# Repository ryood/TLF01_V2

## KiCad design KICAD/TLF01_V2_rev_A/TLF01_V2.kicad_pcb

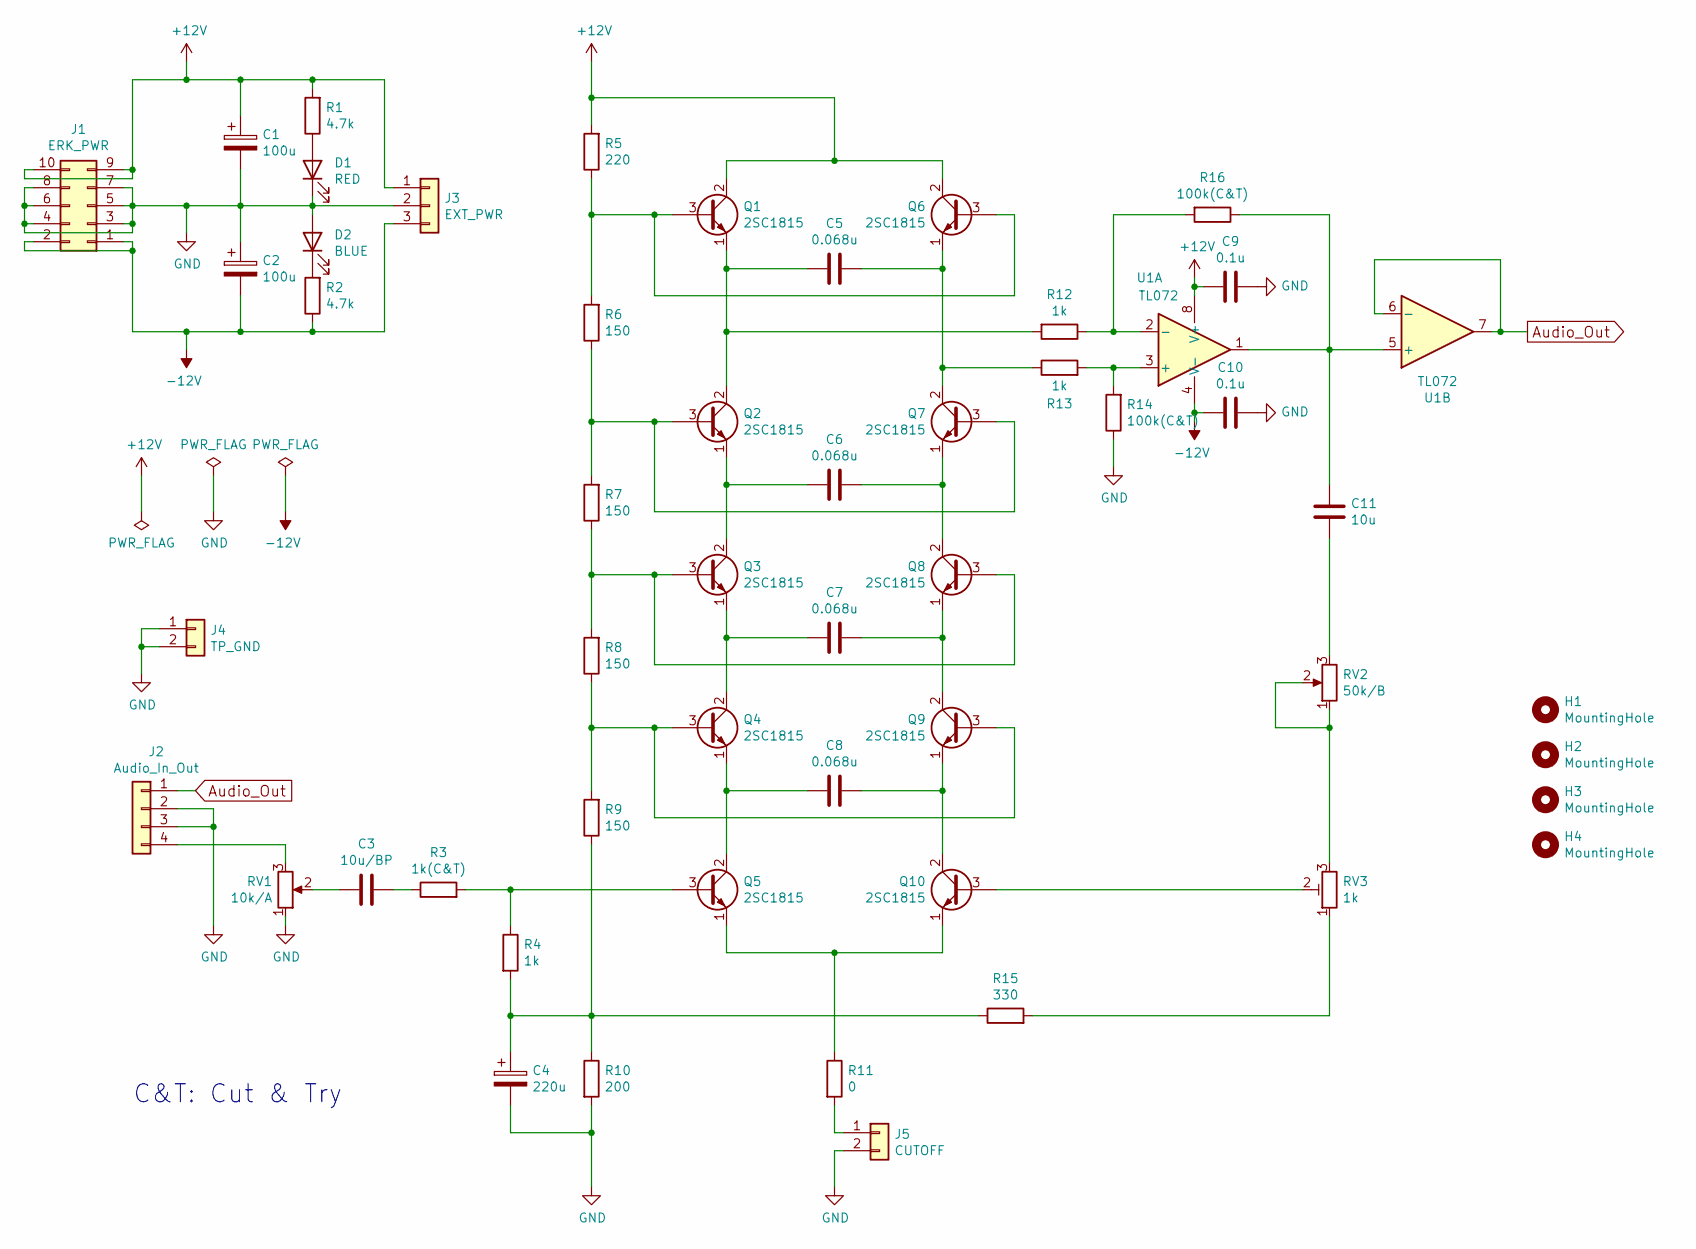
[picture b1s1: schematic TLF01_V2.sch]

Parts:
C1, C2: 100u; CP_Radial_D8.0mm_P2.50mm
C3: 10u/BP; CP_Radial_D6.3mm_P2.50mm
C4: 220u; CP_Radial_D8.0mm_P2.50mm
C5, C6, C7, C8: 0.068u; C_Rect_L10.0mm_W4.0mm_P7.50mm_MKS4
C9, C10: 0.1u; C_Disc_D3.0mm_W1.6mm_P2.50mm
C11: 10u; C_Radial_D10.0mm_H12.5mm_P5.00mm
D1: RED; LED_D3.0mm
D2: BLUE; LED_D3.0mm
H1, H2, H3, H4: MountingHole; MountingHole_3.2mm_M3
J1: ERK_PWR; IDC-Header_2x05_P2.54mm_Vertical
J2: Audio_In_Out; JST_XH_B4B-XH-A_1x04_P2.50mm_Vertical
J3: EXT_PWR; JST_XH_B3B-XH-A_1x03_P2.50mm_Vertical
J4: TP_GND; PinHeader_1x02_P2.54mm_Vertical
J5: CUTOFF; JST_XH_B2B-XH-A_1x02_P2.50mm_Vertical
Q1, Q2, Q3, Q4, Q5, Q6, Q7, Q8, Q9, Q10: 2SC1815; TO-92_Wide
R1, R2: 4.7k; R_Axial_DIN0207_L6.3mm_D2.5mm_P7.62mm_Horizontal
R3: 1k(C&T); R_Axial_DIN0207_L6.3mm_D2.5mm_P7.62mm_Horizontal
R4, R12, R13: 1k; R_Axial_DIN0207_L6.3mm_D2.5mm_P7.62mm_Horizontal
R5: 220; R_Axial_DIN0207_L6.3mm_D2.5mm_P7.62mm_Horizontal
R6, R7, R8, R9: 150; R_Axial_DIN0207_L6.3mm_D2.5mm_P7.62mm_Horizontal
R10: 200; R_Axial_DIN0207_L6.3mm_D2.5mm_P7.62mm_Horizontal
R11: 0; R_Axial_DIN0207_L6.3mm_D2.5mm_P7.62mm_Horizontal
R14, R16: 100k(C&T); R_Axial_DIN0207_L6.3mm_D2.5mm_P7.62mm_Horizontal
R15: 330; R_Axial_DIN0207_L6.3mm_D2.5mm_P7.62mm_Horizontal
RV1: 10k/A; Potentiometer_Alps_RK097_Single_Horizontal
RV2: 50k/B; Potentiometer_Alps_RK097_Single_Horizontal
RV3: 1k; Potentiometer_Bourns_3362P_Vertical
U1: TL072; DIP-8_W7.62mm_LongPads

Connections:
+12V: C1.1, C9.2, J1.9, J1.10, J3.1, Q1.2 (C), Q6.2 (C), R1.2, R5.2, U1.8 (V+)
-12V: C2.2, C10.2, J1.1, J1.2, J3.3, R2.1, U1.4 (V-)
Audio_Out: J2.1, U1.6 (-), U1.7
GND: C1.2, C2.1, C4.2, C9.1, C10.1, D1.1 (K), D2.2 (A), J1.3, J1.4, J1.5, J1.6, J1.7, J1.8, J2.2, J2.3, J3.2, J4.1, J4.2, J5.2, R10.2, R14.1, RV1.1
unnamed: C3.1, R3.1
unnamed: C3.2, RV1.2
unnamed: C4.1, R4.2, R9.1, R10.1, R15.1
unnamed: C5.1, Q6.1 (E), Q7.2 (C), R13.1
unnamed: C5.2, Q1.1 (E), Q2.2 (C), R12.2
unnamed: C6.1, Q7.1 (E), Q8.2 (C)
unnamed: C6.2, Q2.1 (E), Q3.2 (C)
unnamed: C7.1, Q8.1 (E), Q9.2 (C)
unnamed: C7.2, Q3.1 (E), Q4.2 (C)
unnamed: C8.1, Q9.1 (E), Q10.2 (C)
unnamed: C8.2, Q4.1 (E), Q5.2 (C)
unnamed: C11.1, RV2.3
unnamed: C11.2, R16.1, U1.1, U1.5 (+)
unnamed: D1.2 (A), R1.1
unnamed: D2.1 (K), R2.2
unnamed: J2.4, RV1.3
unnamed: J5.1, R11.2
unnamed: Q1.3 (B), Q6.3 (B), R5.1, R6.2
unnamed: Q2.3 (B), Q7.3 (B), R6.1, R7.2
unnamed: Q3.3 (B), Q8.3 (B), R7.1, R8.2
unnamed: Q4.3 (B), Q9.3 (B), R8.1, R9.2
unnamed: Q5.3 (B), R3.2, R4.1
unnamed: Q5.1 (E), Q10.1 (E), R11.1
unnamed: Q10.3 (B), RV3.2
unnamed: R12.1, R16.2, U1.2 (-)
unnamed: R13.2, R14.2, U1.3 (+)
unnamed: R15.2, RV3.1
unnamed: RV2.1, RV2.2, RV3.3

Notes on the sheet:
C&T: Cut & Try

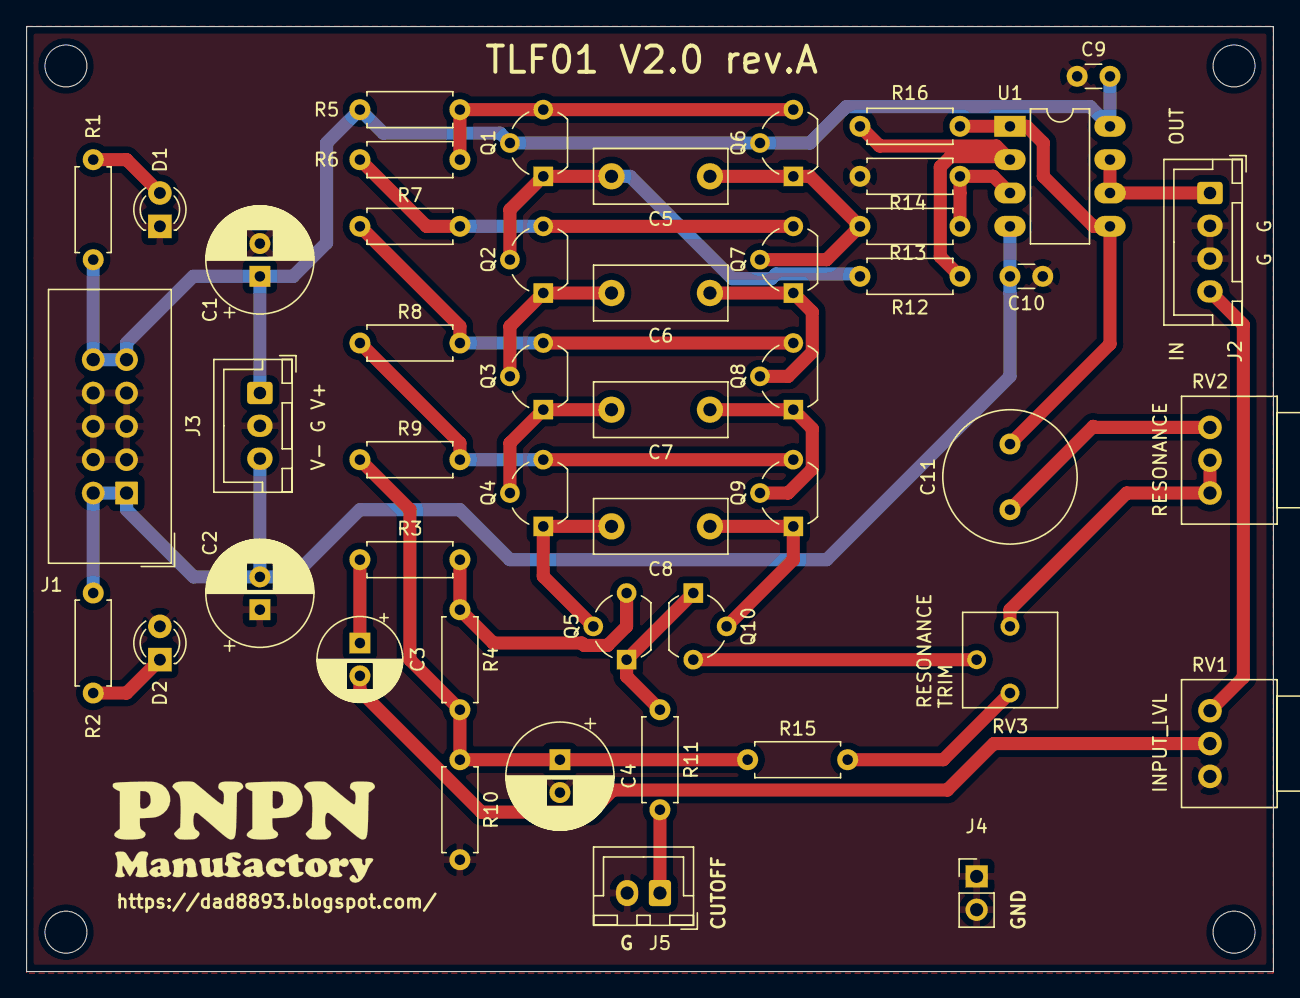
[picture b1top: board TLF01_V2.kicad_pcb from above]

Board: 2 copper layers, 95.0 x 72.0 mm, 52 parts (0 on the bottom side), 32 nets.

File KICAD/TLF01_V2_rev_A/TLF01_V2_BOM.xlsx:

Reference | Quantity | Value | Footprint
C1 C2 | 2 | 100u | Capacitor_THT:CP_Radial_D8.0mm_P2.50mm
C11 | 1 | 10u | Capacitor_THT:C_Radial_D10.0mm_H12.5mm_P5.00mm
C3 | 1 | 10u | Capacitor_THT:CP_Radial_D6.3mm_P2.50mm
C4 | 1 | 220u | Capacitor_THT:CP_Radial_D8.0mm_P2.50mm
C5 C6 C7 C8 | 4 | 0.068u | Capacitor_THT:C_Rect_L10.0mm_W4.0mm_P7.50mm_MKS4
C9 C10 | 2 | 0.1u | Capacitor_THT:C_Disc_D3.0mm_W1.6mm_P2.50mm
D1 | 1 | RED | LED_THT:LED_D3.0mm
D2 | 1 | BLUE | LED_THT:LED_D3.0mm
H1 H2 H3 H4 | 4 | MountingHole | MountingHole:MountingHole_3.2mm_M3
J1 | 1 | ERK_PWR | Connector_IDC:IDC-Header_2x05_P2.54mm_Vertical
J2 | 1 | AUDIO_IN | Connector_PinHeader_2.54mm:PinHeader_1x02_P2.54mm_Vertical
J3 | 1 | EXT_PWR | Connector_JST:JST_XH_B3B-XH-A_1x03_P2.50mm_Vertical
J4 | 1 | TP_GND | Connector_PinHeader_2.54mm:PinHeader_1x02_P2.54mm_Vertical
J5 | 1 | CUTOFF | Connector_PinHeader_2.54mm:PinHeader_1x02_P2.54mm_Vertical
J6 | 1 | AUDIO_OUT | Connector_PinHeader_2.54mm:PinHeader_1x02_P2.54mm_Vertical
Q1 Q2 Q6 Q7 Q3 Q8 Q4 Q9 Q5 Q10 | 10 | 2SC1815 | Package_TO_SOT_THT:TO-92_Inline
R1 R2 | 2 | 4.7k | Resistor_THT:R_Axial_DIN0207_L6.3mm_D2.5mm_P7.62mm_Horizontal
R10 | 1 | 200 | Resistor_THT:R_Axial_DIN0207_L6.3mm_D2.5mm_P7.62mm_Horizontal
R11 | 1 | 0 | Resistor_THT:R_Axial_DIN0207_L6.3mm_D2.5mm_P7.62mm_Horizontal
R13 R3 R12 | 3 | 1k(C&T) | Resistor_THT:R_Axial_DIN0207_L6.3mm_D2.5mm_P7.62mm_Horizontal
R14 R16 | 2 | 100k | Resistor_THT:R_Axial_DIN0207_L6.3mm_D2.5mm_P7.62mm_Horizontal
R15 | 1 | 330 | Resistor_THT:R_Axial_DIN0207_L6.3mm_D2.5mm_P7.62mm_Horizontal
R4 | 1 | 1k | Resistor_THT:R_Axial_DIN0207_L6.3mm_D2.5mm_P7.62mm_Horizontal
R5 | 1 | 220 | Resistor_THT:R_Axial_DIN0207_L6.3mm_D2.5mm_P7.62mm_Horizontal
R6 R7 R8 R9 | 4 | 150 | Resistor_THT:R_Axial_DIN0207_L6.3mm_D2.5mm_P7.62mm_Horizontal
RV1 | 1 | 10k/A | Potentiometer_THT:Potentiometer_Alps_RK097_Single_Horizontal
RV2 | 1 | 50k/B | Potentiometer_THT:Potentiometer_Alps_RK097_Single_Horizontal
RV3 | 1 | 1k | Potentiometer_THT:Potentiometer_Bourns_3386P_Vertical
U1 | 1 | TL072 | Package_DIP:DIP-8_W7.62mm_LongPads

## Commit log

2020-05-05 PCB Design
2020-06-26 Update PCB Design
2020-08-15 Update: PCB Design
2020-08-17 Update: spice files
2020-08-25 Add: AC波形
2020-10-17 Gerber
2021-04-08 Rev.A Implementation
2022-08-30 Spice sim
2022-08-30 Update panel design
2022-09-11 Add 2 in 1 Panel
